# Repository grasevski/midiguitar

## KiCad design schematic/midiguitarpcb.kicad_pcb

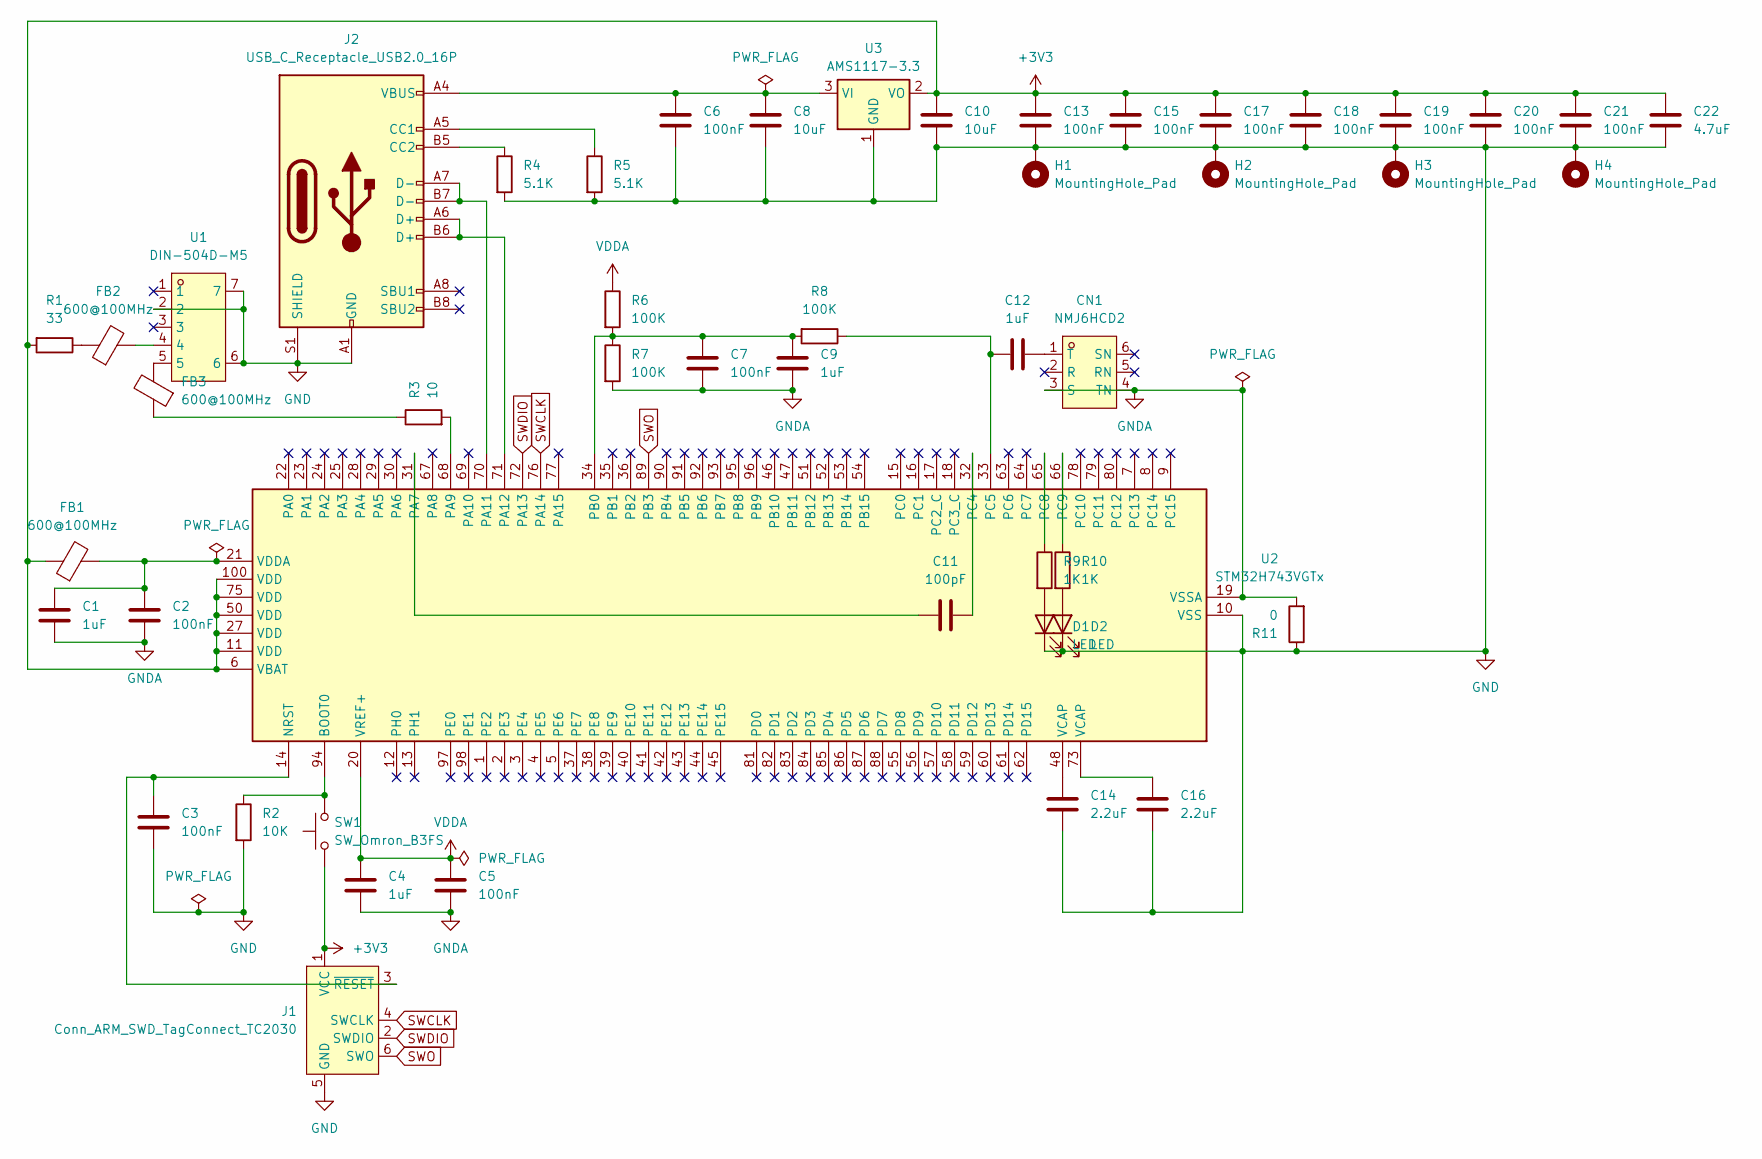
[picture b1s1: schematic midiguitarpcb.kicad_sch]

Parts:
C1, C4, C9, C12: 1uF; C_0603_1608Metric
C2, C3, C5, C6, C7, C13, C15, C17, C18, C19, C20, C21: 100nF; C_0603_1608Metric
C8, C10: 10uF; C_0603_1608Metric
C11: 100pF; C_0603_1608Metric
C14, C16: 2.2uF; C_0603_1608Metric
C22: 4.7uF; C_0603_1608Metric
CN1: NMJ6HCD2; AUDIO-TH_NMJ6HCD2; LCSC Part C368502
D1, D2: LED; LED_0603_1608Metric
FB1, FB2, FB3: 600@100MHz; L_0603_1608Metric
H1, H2, H3, H4: MountingHole_Pad; MountingHole_3.2mm_M3_Pad
J1: Conn_ARM_SWD_TagConnect_TC2030; Tag-Connect_TC2030-IDC-FP_2x03_P1.27mm_Vertical
J2: USB_C_Receptacle_USB2.0_16P; USB_C_Receptacle_HRO_TYPE-C-31-M-12
R1: 33; R_0603_1608Metric
R2: 10K; R_0603_1608Metric
R3: 10; R_0603_1608Metric
R4, R5: 5.1K; R_0603_1608Metric
R6, R7, R8: 100K; R_0603_1608Metric
R9, R10: 1K; R_0603_1608Metric
R11: 0; R_0603_1608Metric
SW1: SW_Omron_B3FS; SW_SPST_Omron_B3FS-100xP
U1: DIN-504D-M5; CONN-TH_DIN-504D-M5; LCSC Part C2939347
U2: STM32H743VGTx; LQFP-100_14x14mm_P0.5mm
U3: AMS1117-3.3; SOT-223-3_TabPin2

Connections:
+3V3: C10.1, C13.1, C15.1, C17.1, C18.1, C19.1, C20.1, C21.1, C22.1, FB1.1, J1.1 (VCC), R1.2, SW1.1, U2.6 (VBAT), U2.11 (VDD), U2.27 (VDD), U2.50 (VDD), U2.75 (VDD), U2.100 (VDD), U3.2 (VO)
GND: C3.1, C6.2, C8.2, C10.2, C13.2, C14.2, C15.2, C16.2, C17.2, C18.2, C19.2, C20.2, C21.2, C22.2, D1.1 (K), D2.1 (K), H1.1, H2.1, H3.1, H4.1, J1.5 (GND), J2.A1 (GND), J2.A12 (GND), J2.B1 (GND), J2.B12 (GND), J2.S1 (SHIELD), R2.2, R4.2, R5.2, R11.1, U1.2, U1.6, U1.7, U2.10 (VSS), U2.26 (VSS), U2.49 (VSS), U2.74 (VSS), U2.99 (VSS), U3.1 (GND)
GNDA: C1.2, C2.2, C4.2, C5.2, C7.2, C9.2, CN1.3 (S), CN1.4 (TN), R7.2, R11.2, U2.19 (VSSA)
unnamed: C14.1, U2.48 (VCAP)
unnamed: C16.1, U2.73 (VCAP)
unnamed: C12.1, CN1.1 (T)
unnamed: D1.2 (A), R9.2
unnamed: D2.2 (A), R10.2
unnamed: FB2.1, R1.1
unnamed: FB2.2, U1.4
unnamed: FB3.1, R3.1
unnamed: FB3.2, U1.5
unnamed: C3.2, J1.3 (~RESET), U2.14 (NRST)
unnamed: J2.A5 (CC1), R5.1
unnamed: J2.B5 (CC2), R4.1
unnamed: R2.1, SW1.2, U2.94 (BOOT0)
unnamed: C11.2, U2.31 (PA7)
unnamed: R3.2, U2.68 (PA9)
unnamed: J2.A7 (D-), J2.B7 (D-), U2.70 (PA11)
unnamed: J2.A6 (D+), J2.B6 (D+), U2.71 (PA12)
unnamed: C7.1, C9.1, R6.2, R7.1, R8.2, U2.34 (PB0)
unnamed: C11.1, U2.32 (PC4)
unnamed: C12.2, R8.1, U2.33 (PC5)
unnamed: R9.1, U2.65 (PC8)
unnamed: R10.1, U2.66 (PC9)
unnamed: C1.1, C2.1, FB1.2, U2.21 (VDDA)
unnamed: C6.1, C8.1, J2.A4 (VBUS), J2.A9 (VBUS), J2.B4 (VBUS), J2.B9 (VBUS), U3.3 (VI)
SWCLK: J1.4 (SWCLK), U2.76 (PA14)
SWDIO: J1.2 (SWDIO), U2.72 (PA13)
SWO: J1.6 (SWO), U2.89 (PB3)
VDDA: C4.1, C5.1, R6.1, U2.20 (VREF+)

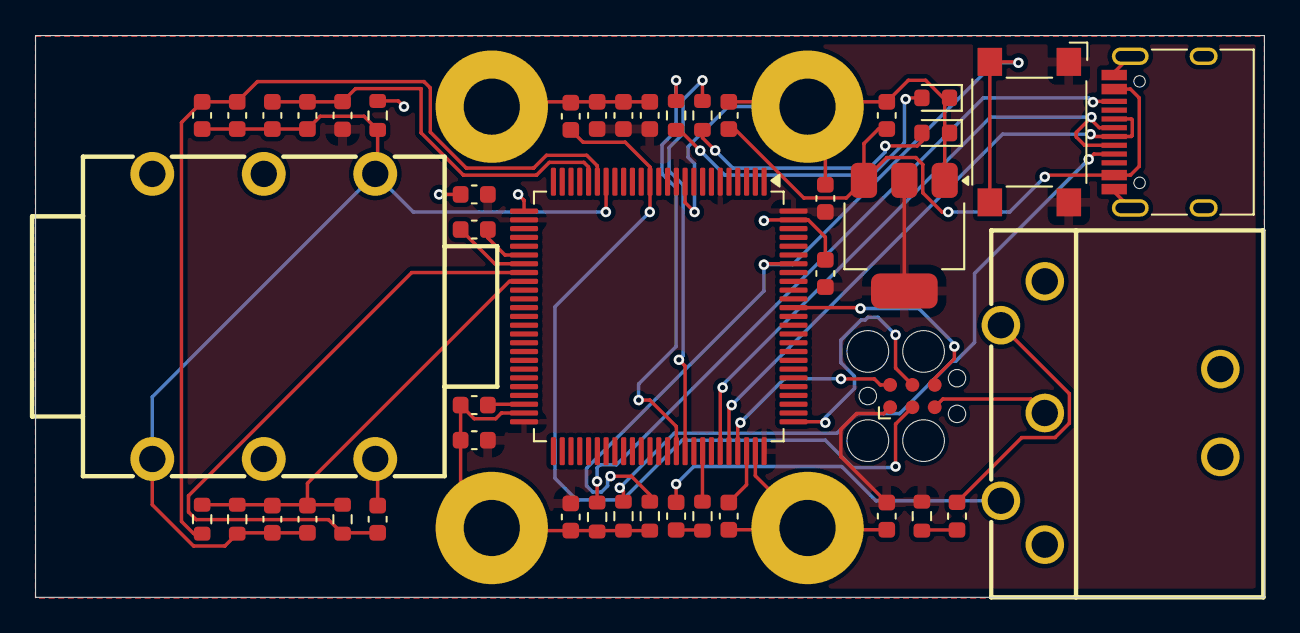
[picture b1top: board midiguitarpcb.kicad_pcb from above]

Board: 2 copper layers, 70.0 x 32.0 mm, 49 parts (0 on the bottom side), 31 nets.

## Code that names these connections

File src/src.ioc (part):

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Mcu.Name=STM32H743VGTx
Mcu.Package=LQFP100
Mcu.UserName=STM32H743VGTx
PA10.Mode=Asynchronous
PA10.Signal=LPUART1_RX
PA11.Mode=Device_Only
PA11.Signal=USB_OTG_FS_DM
PA12.Mode=Device_Only
PA12.Signal=USB_OTG_FS_DP
PA13\ (JTMS/SWDIO).Mode=Trace_Asynchronous_SW
PA13\ (JTMS/SWDIO).Signal=DEBUG_JTMS-SWDIO
PA14\ (JTCK/SWCLK).Mode=Trace_Asynchronous_SW
PA14\ (JTCK/SWCLK).Signal=DEBUG_JTCK-SWCLK
PA7.Mode=PGA Connected-INVERTINGINPUT_IO0_IO1_BIAS
PA7.Signal=OPAMP1_VINM1
PA9.Mode=Asynchronous
PA9.Signal=LPUART1_TX
PB0.Mode=PGA Connected-INVERTINGINPUT_IO0_IO1_BIAS
PB0.Signal=OPAMP1_VINP
PB3\ (JTDO/TRACESWO).Mode=Trace_Asynchronous_SW
PB3\ (JTDO/TRACESWO).Signal=DEBUG_JTDO-SWO
PC4.Mode=PGA Connected-INVERTINGINPUT_IO0_IO1_BIAS
PC4.Signal=OPAMP1_VOUT
PC5.Mode=PGA Connected-INVERTINGINPUT_IO0_IO1_BIAS
PC5.Signal=OPAMP1_VINM0
PC8.Signal=GPIO_Output
PC9.Signal=GPIO_Output
RCC.SYSCLKFreq_VALUE=480000000
RCC.SYSCLKSource=RCC_SYSCLKSOURCE_PLLCLK
board=custom

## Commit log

2026-01-05 wip working but noisy
2026-01-14 redo pcb
2026-01-22 wip about to put in mounting holes
2026-01-27 wip about to put leds in
2026-02-02 skinny pcb
2026-02-09 fix lpuart
2026-02-12 fix(midi): only 7 bits
2026-02-14 wip working ok now
2026-02-14 bit more within time budget
2026-02-15 sluggish but ok settings
2026-02-15 chore(style): rename variables
2026-02-24 feat(perf): speed up sin cos calculation
    Also let windows overlap immediately rather than waiting for a preset
    window size. And set FFT size equal to data size. It may perform better
    if FFT size is bigger than data size, for instance 5NL where N is data
    size and L is max model order, like in the fastf0nls paper where this
    was found to be a good setting. This may be worth testing.
2026-02-26 feat(perf): parabolic interpolation
    Calculate 3 points and interpolate rather than doing golden search.
2026-02-28 Revert "feat(perf): parabolic interpolation"
    This reverts commit 6bac09e98bdb278f92eac39c7946ee6c08b5e237.
2026-03-01 fix thp
2026-03-01 maximize accuracy
2026-03-02 feat(perf): reinstate zero padding
    See if it runs faster to use zero padding rather than the entire 4096
    samples for the grid.
2026-03-03 chore(perf): better sample size
